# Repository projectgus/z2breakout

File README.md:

**This is an abandoned alpha-quality design at this point, unless someone wants to pick it up. I built some prototypes in late 2013 and the USB connector & boost converter are verified, but there's some [known problems with the connector pinout](https://github.com/projectgus/z2breakout/issues/1) and the silkscreen is also pretty messy, the whole board probably needs to grow for more labelling space.**

## Z2 Breakout module

A breakout board for the "ZipIt Z2" dock connector. Alpha-quality at the moment.

Design files created with Kicad 2013-Mar-13-testing (this version or newer is probably required.)

Breaks out dock connector to provide:
* USB A & USB Micro B connectors (only one can be used at a time.)
* Camera header for a OV7670 camera module (untested), doubles as GPIO header.
* Dedicated i2c header with 3.3V power pins
* Other breakout headers for power, onboard "headphone remote" ADC, microphone input, "BTRXD" UART pin.
* PCB contains area to build a 3.3V -> 5V boost converter based on TI TPS61240, which can be jumpered to the USB A connector. This is so the USB A connector can be used when the ZipIt is running on battery.

NB: The 3.3V power supply in the ZipIt does not contain enough capacity to output 500mA @ 5V. (If you've measured the surplus current capacity of the 3.3V supply, please let me know and I'll post it here!)

Z2 Breakout design is Copyright (C) 2013 Angus Gratton, released under the TAPR OHL as described in the included file "LICENSE".

Comes with absolutely no warranty, may not work, etc. Not endorsed by or otherwise related to the company ZipIt Wireless.

# Known Issues

* Libraries are a bit of a mess, lots of piecemeal .mod files. Due for a cleanup.

* Did I mention it hasn't been successfully made or used yet? Good. :)

# Resources

Based on the excellent research done by other Z2 owners, and the information [released by ZipIt Wireless themselves](http://linux.zipitwireless.com/):

* http://bealecorner.org/best/measure/z2/z2-connector-pinout-2011.txt

* http://embeddedprogrammer.blogspot.com.au/2012/07/hacking-ov7670-camera-module-sccb-cheat.html

If you're looking for more ZipIt Z2 hacking stuff, try:

* #zipit IRC channel on Freenode
* http://www.mozzwald.com/
* http://chainxor.org/openwrt-zipit/

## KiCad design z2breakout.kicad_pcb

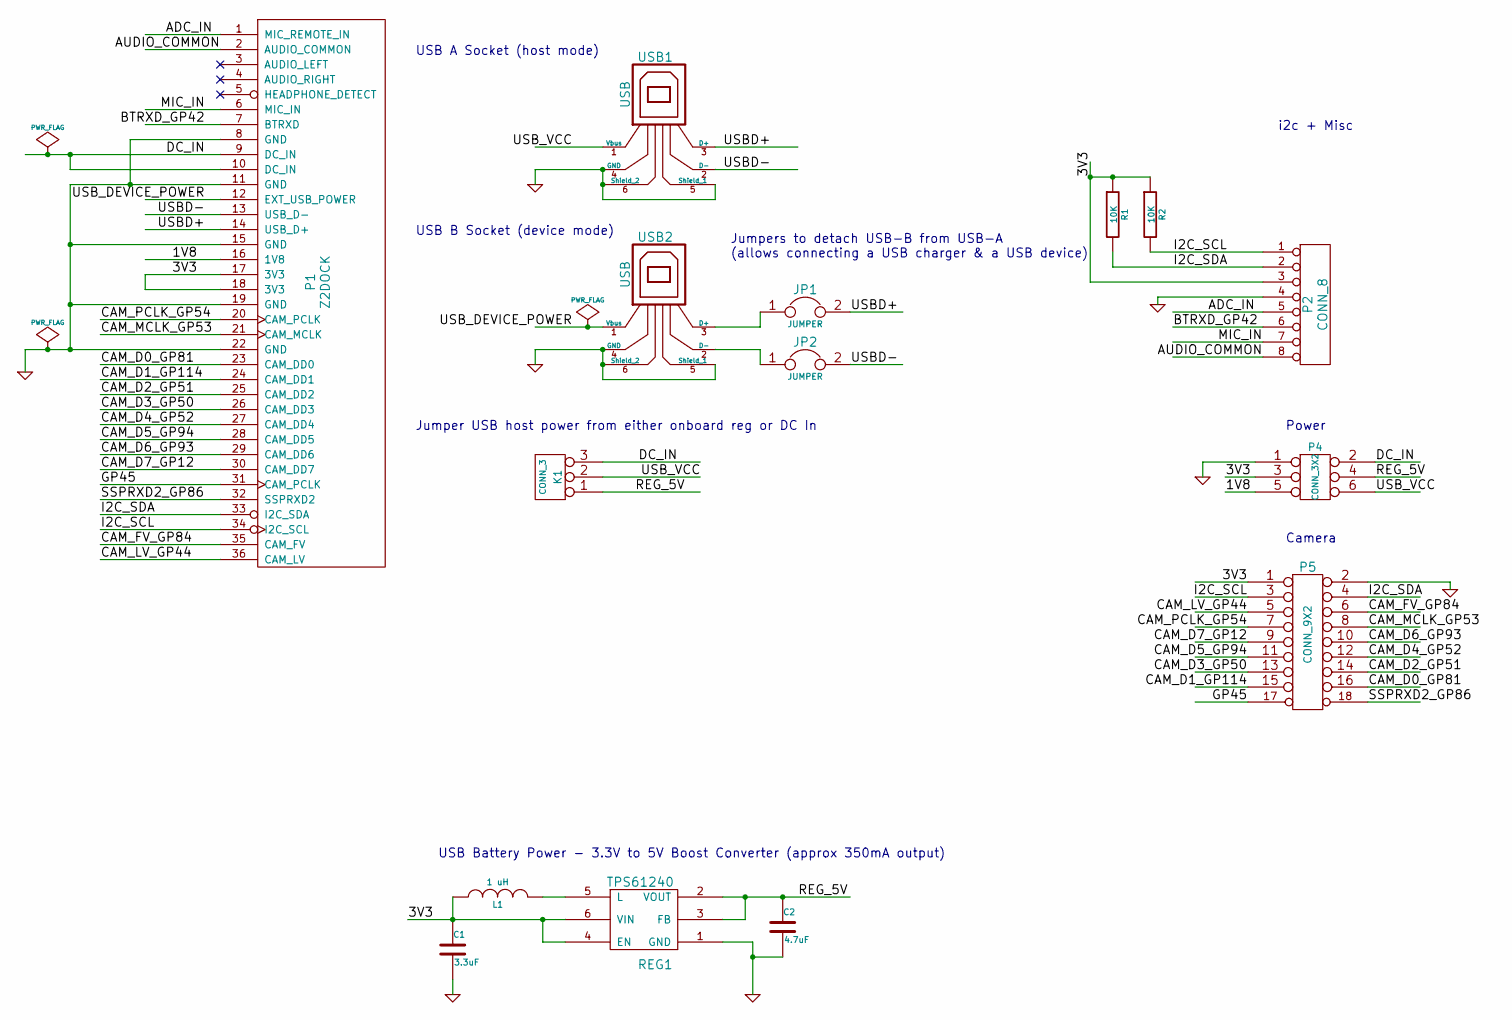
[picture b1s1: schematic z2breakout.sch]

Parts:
C1: 3.3uF
C2: 4.7uF
JP1, JP2: JUMPER
K1: CONN_3
L1: 1 uH
P1: Z2DOCK
P2: CONN_8
P4: CONN_3X2
P5: CONN_9X2
R1, R2: 10K
REG1: TPS61240
USB1, USB2: USB

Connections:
/1V8: P1.16 (1V8), P4.5
/3V3: C1.1, L1.1, P1.17 (3V3), P1.18 (3V3), P2.3, P4.3, P5.1, R1.1, R2.1, REG1.4 (EN), REG1.6 (VIN)
/ADC_IN: P1.1 (MIC_REMOTE_IN), P2.5
/AUDIO_COMMON: P1.2 (AUDIO_COMMON), P2.8
/BTRXD_GP42: P1.7 (BTRXD), P2.6
/CAM_D0_GP81: P1.23 (CAM_DD0), P5.16
/CAM_D1_GP114: P1.24 (CAM_DD1), P5.15
/CAM_D2_GP51: P1.25 (CAM_DD2), P5.14
/CAM_D3_GP50: P1.26 (CAM_DD3), P5.13
/CAM_D4_GP52: P1.27 (CAM_DD4), P5.12
/CAM_D5_GP94: P1.28 (CAM_DD5), P5.11
/CAM_D6_GP93: P1.29 (CAM_DD6), P5.10
/CAM_D7_GP12: P1.30 (CAM_DD7), P5.9
/CAM_FV_GP84: P1.35 (CAM_FV), P5.6
/CAM_LV_GP44: P1.36 (CAM_LV), P5.5
/CAM_MCLK_GP53: P1.21 (CAM_MCLK), P5.8
/CAM_PCLK_GP54: P1.20 (CAM_PCLK), P5.7
/DC_IN: K1.3, P1.9 (DC_IN), P1.10 (DC_IN), P4.2
/GP45: P1.31 (CAM_PCLK), P5.17
/I2C_SCL: P1.34 (I2C_SCL), P2.1, P5.3, R2.2
/I2C_SDA: P1.33 (I2C_SDA), P2.2, P5.4, R1.2
/MIC_IN: P1.6 (MIC_IN), P2.7
/REG_5V: C2.1, K1.1, P4.4, REG1.2 (VOUT), REG1.3 (FB)
/SSPRXD2_GP86: P1.32 (SSPRXD2), P5.18
/USBD+: JP1.2, P1.14 (USB_D+), USB1.3 (D+)
/USBD-: JP2.2, P1.13 (USB_D-), USB1.2 (D-)
/USB_DEVICE_POWER: P1.12 (EXT_USB_POWER), USB2.1 (Vbus)
/USB_VCC: K1.2 (PM), P4.6, USB1.1 (Vbus)
GND: C1.2, C2.2, P1.8 (GND), P1.11 (GND), P1.15 (GND), P1.19 (GND), P1.22 (GND), P2.4, P4.1, P5.2, REG1.1 (GND), USB1.4 (GND), USB1.5 (Shield_1), USB1.6 (Shield_2), USB2.4 (GND), USB2.5 (Shield_1), USB2.6 (Shield_2)
unnamed: JP1.1, USB2.3 (D+)
unnamed: JP2.1, USB2.2 (D-)
unnamed: L1.2, REG1.5 (L)

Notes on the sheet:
USB A Socket (host mode)
USB B Socket (device mode)
i2c + Misc
Power
USB Battery Power - 3.3V to 5V Boost Converter (approx 350mA output)
Camera
Jumpers to detach USB-B from USB-A (allows connecting a USB charger & a USB device)
Jumper USB host power from either onboard reg or DC In

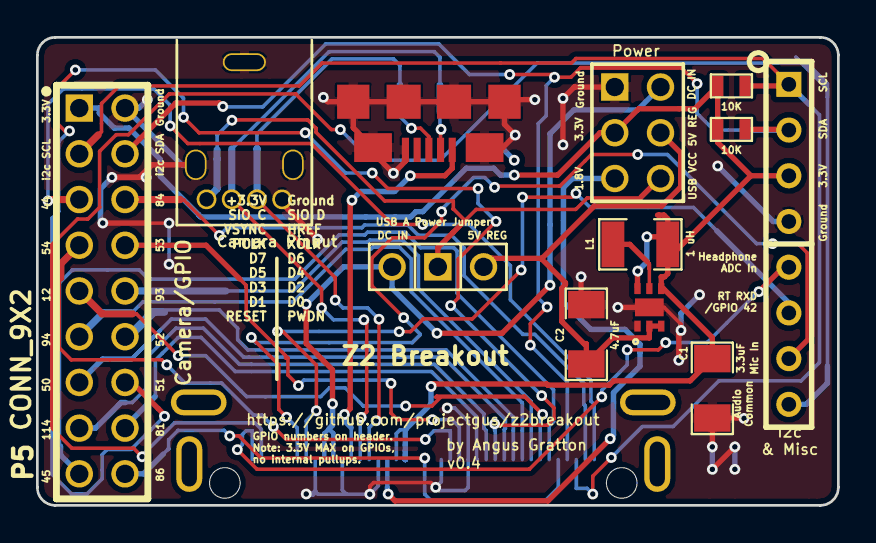
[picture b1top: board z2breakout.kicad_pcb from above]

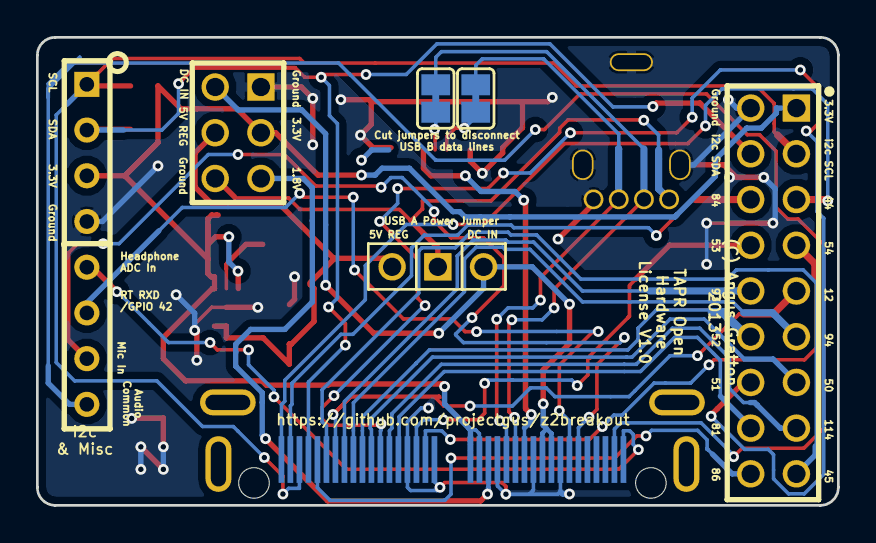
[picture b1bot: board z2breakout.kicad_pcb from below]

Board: 2 copper layers, 44.5 x 26.0 mm, 15 parts (3 on the bottom side), 32 nets.

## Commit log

2013-05-14 Start from previous design schematic, etc.
2013-06-25 Finish design, first cut of board layout for prototyping
2013-06-25 Add gitignore
2013-06-25 Add license (TAPR OHL)
2013-06-25 Add a README
2013-06-25 Rename zipitbreakout to z2breakout
2013-07-16 ST60X-36S: Fix backwards pin order, extend pads for easier hand soldering, add PCB edge/connector extent positioning lines
2013-07-16 ST60X-36S: Widen pad lands from 0.3mm to 0.32mm as per datasheet
2013-07-19 Fix footprint for upright USB A connector
2013-09-17 Reroute with correct pin order, better connector spacing
2013-09-18 Fix up silkscreen, try to improve grounding
2013-11-07 Clean up silkscreen a bit, add i2c pullup resistors
2014-11-18 Add a note pointing to @mozzwald's bug report
